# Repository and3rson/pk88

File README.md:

# PK88

Single-board computer based on KM1810VM88 CPU (Ukrainian clone of Intel 8088) that can run ELKS!

PK stands for Персональний Комп'ютер ("Personalnii Kompyuter", i.e. "Personal Computer") in Ukrainian.

This board runs @ 8 MHz (24 MHz oscillator) in minimum mode.

- [KiCad schematics](./kicad)
- [GAL sources](./gal) - Address & I/O port decoders using 2x ATF16V8
- [Various circuit simulations](./circuits) - made with [Digital](https://github.com/hneemann/Digital)
- [MetalBIOS](./metalbios) - IBM PC XT compatible-ish BIOS that I made specifically for PK-88

## Resources

- 8088/x86 instruction set: <https://zsmith.co/intel.php>
- Zen of Assembly language (including 8088 instruction set): <http://www.jagregory.com/abrash-zen-of-asm/>
- Soviet IC series differences: <http://vozom.ho.ua/R4/page21.html>
- IBM PC technical reference: <http://bitsavers.informatik.uni-stuttgart.de/pdf/ibm/pc/at/6183355_PC_AT_Technical_Reference_Mar86.pdf>

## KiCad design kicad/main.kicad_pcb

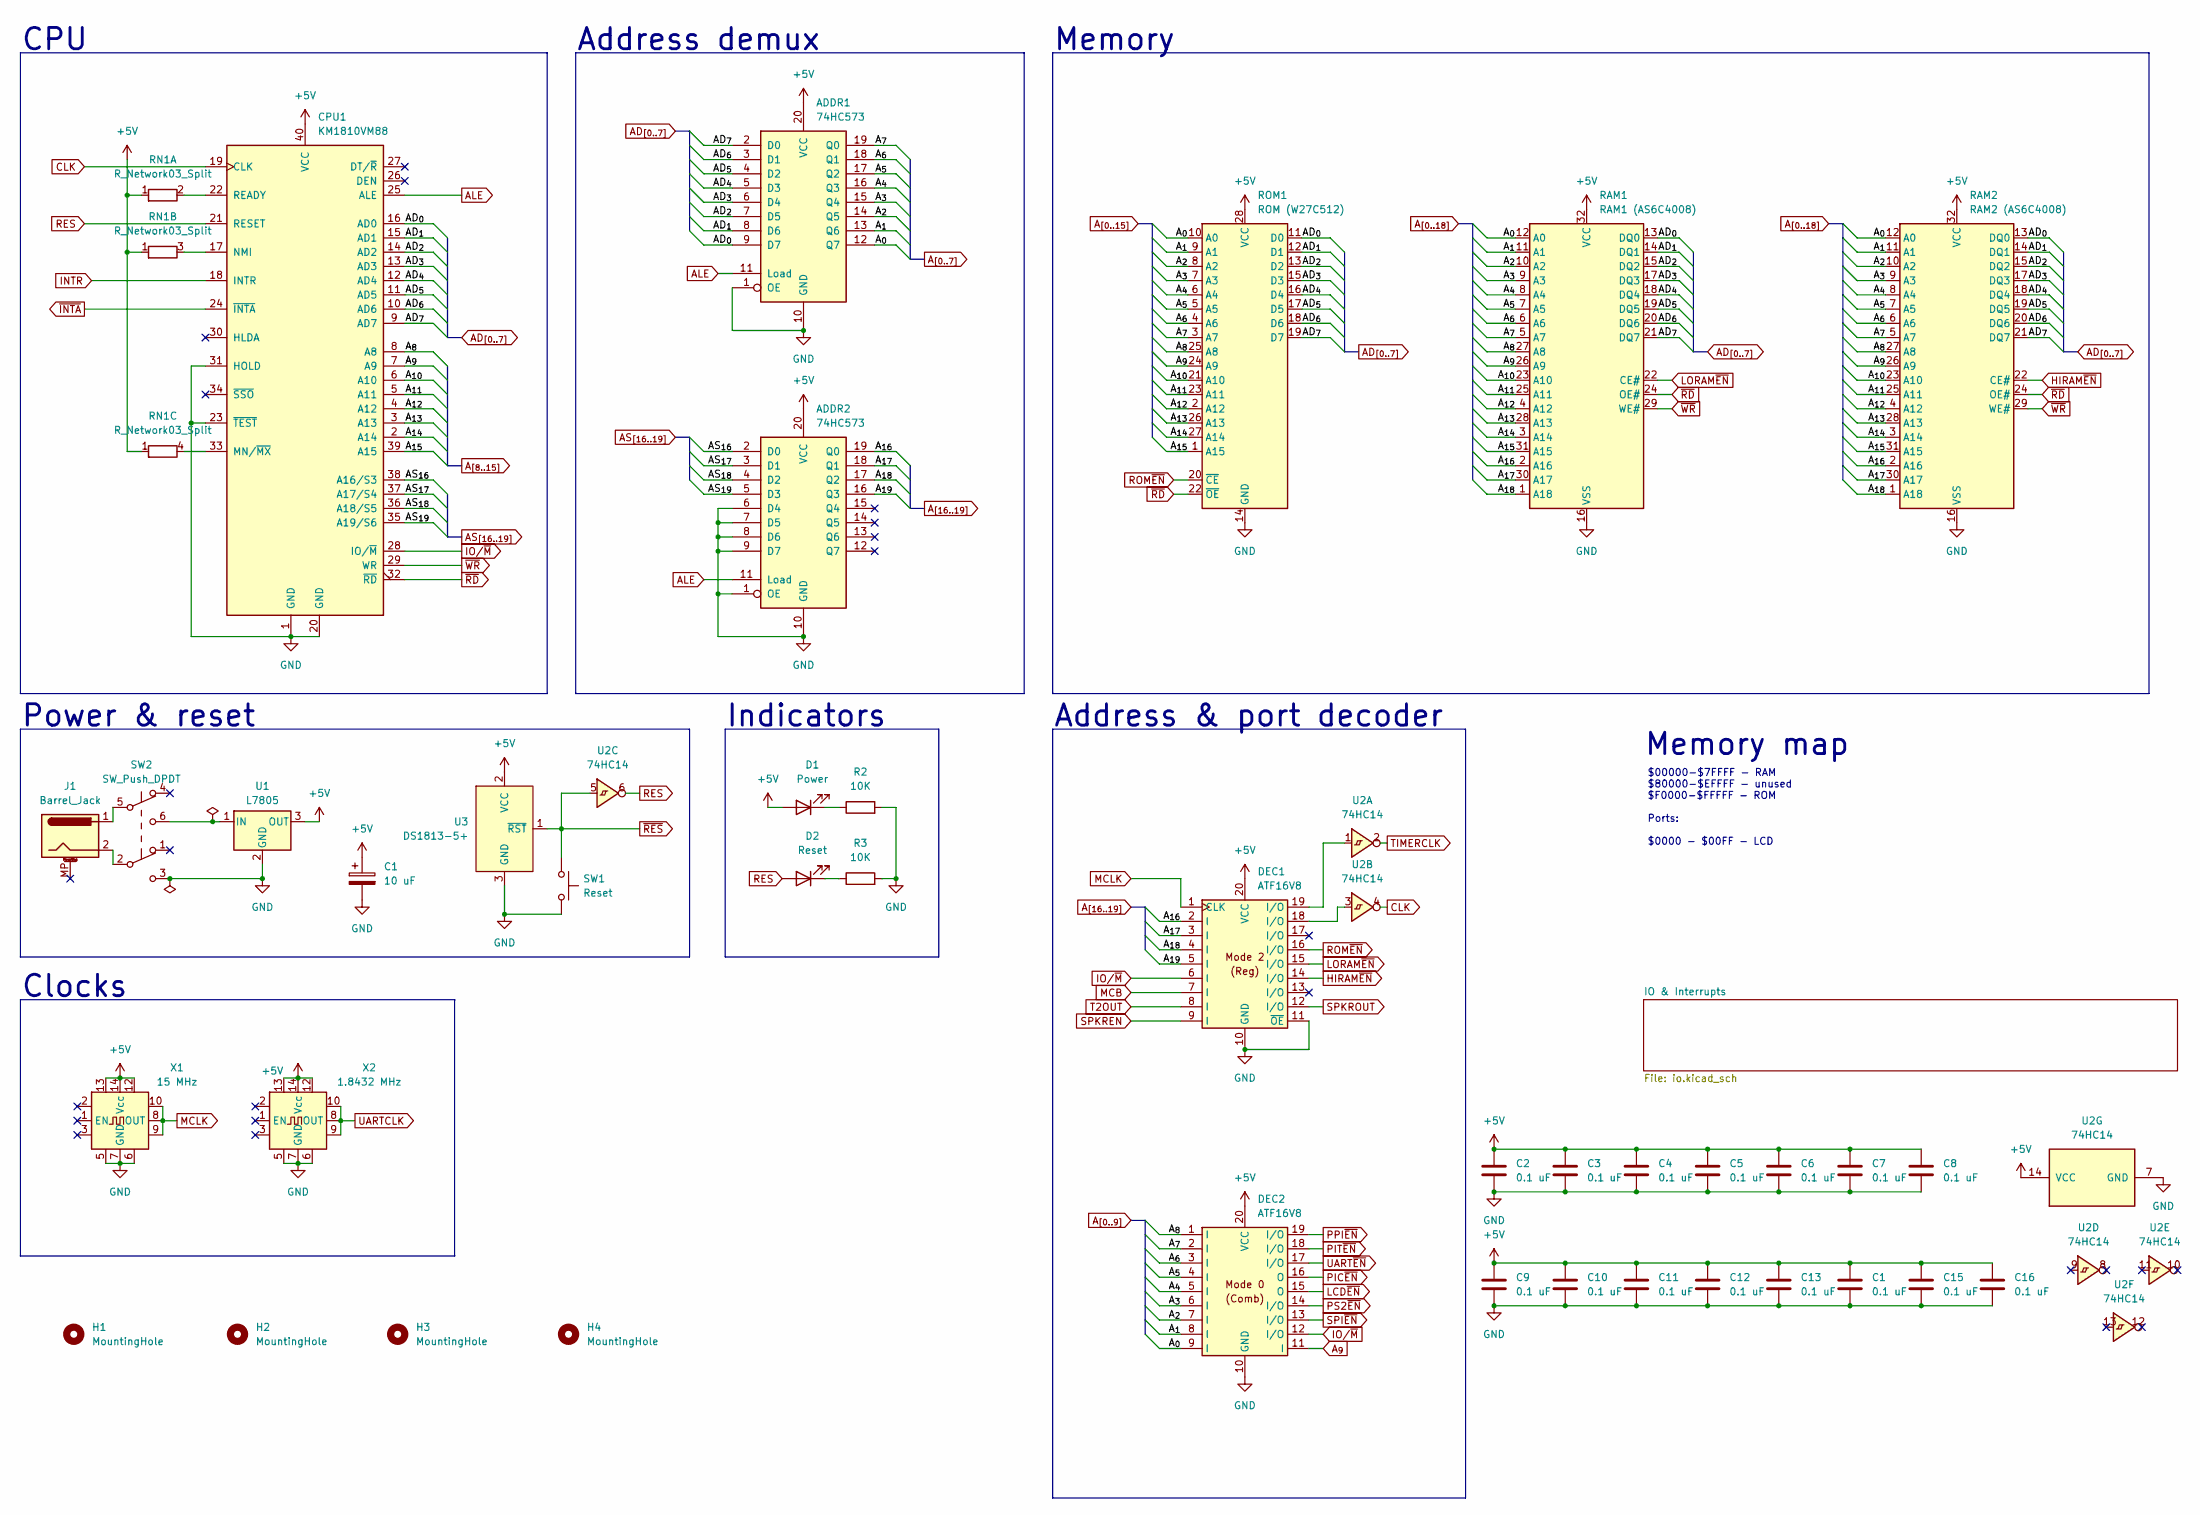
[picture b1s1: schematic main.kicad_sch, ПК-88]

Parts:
ADDR1, ADDR2: 74HC573; DIP-20_W7.62mm_Socket
C1: 10 uF; CP_Radial_D8.0mm_P3.50mm
C2, C4, C5, C7, C8, C10, C15, C16: 0.1 uF; C_Disc_Long
C3, C11: 0.1 uF; C_Disc_D3.0mm_W1.6mm_P2.50mm
C6, C9, C12, C13: 0.1 uF; C_Disc_VeryLong
CPU1: KM1810VM88; DIP-40_W15.24mm
D1: Power; LED_D3.0mm
D2: Reset; LED_D3.0mm
DEC1, DEC2: ATF16V8; DIP-20_W7.62mm_Socket
H1, H2, H3, H4: MountingHole; Hole_3.5x5
J1: Barrel_Jack; BarrelJack_Wuerth_6941xx301002
R2, R3: 10K; R_Axial_DIN0204_L3.6mm_D1.6mm_P7.62mm_Horizontal
RAM1: RAM1 (AS6C4008); DIP-32_W15.24mm
RAM2: RAM2 (AS6C4008); DIP-32_W15.24mm
RN1: R_Network03_Split; R_Array_SIP4
ROM1: ROM (W27C512); ZIF28
SW1: Reset; SW_PUSH_6mm_H5mm
SW2: SW_Push_DPDT; PB22E06
U1: L7805; TO-220-3_Vertical
U2: 74HC14; DIP-14_W7.62mm_Socket
U3: DS1813-5+; TO-92L_Inline_Wide
X1: 15 MHz; Oscillator_DIP-8-14
X2: 1.8432 MHz; Oscillator_DIP-8-14

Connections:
+5V: ADDR1.20 (VCC), ADDR2.20 (VCC), C1.1, C2.1, C3.1, C4.1, C5.1, C6.1, C7.1, C8.1, C9.1, C10.1, C11.1, C12.1, C13.1, C15.1, C16.1, CPU1.40 (VCC), D1.2 (A), DEC1.20 (VCC), DEC2.20 (VCC), RAM1.32 (VCC), RAM2.32 (VCC), RN1.1 (R1), ROM1.28 (VCC), U1.3 (OUT), U2.14 (VCC), U3.2 (VCC), X1.12, X1.13, X1.14 (Vcc), X2.12, X2.13, X2.14 (Vcc); also elsewhere on the board
AD_{0}: ADDR1.9 (D7), CPU1.16 (AD0), RAM1.13 (DQ0), RAM2.13 (DQ0), ROM1.11 (D0); also elsewhere on the board
AD_{1}: ADDR1.8 (D6), CPU1.15 (AD1), RAM1.14 (DQ1), RAM2.14 (DQ1), ROM1.12 (D1); also elsewhere on the board
AD_{2}: ADDR1.7 (D5), CPU1.14 (AD2), RAM1.15 (DQ2), RAM2.15 (DQ2), ROM1.13 (D2); also elsewhere on the board
AD_{3}: ADDR1.6 (D4), CPU1.13 (AD3), RAM1.17 (DQ3), RAM2.17 (DQ3), ROM1.15 (D3); also elsewhere on the board
AD_{4}: ADDR1.5 (D3), CPU1.12 (AD4), RAM1.18 (DQ4), RAM2.18 (DQ4), ROM1.16 (D4); also elsewhere on the board
AD_{5}: ADDR1.4 (D2), CPU1.11 (AD5), RAM1.19 (DQ5), RAM2.19 (DQ5), ROM1.17 (D5); also elsewhere on the board
AD_{6}: ADDR1.3 (D1), CPU1.10 (AD6), RAM1.20 (DQ6), RAM2.20 (DQ6), ROM1.18 (D6); also elsewhere on the board
AD_{7}: ADDR1.2 (D0), CPU1.9 (AD7), RAM1.21 (DQ7), RAM2.21 (DQ7), ROM1.19 (D7); also elsewhere on the board
ALE: ADDR1.11 (Load), ADDR2.11 (Load), CPU1.25 (ALE)
AS_{16}: ADDR2.2 (D0), CPU1.38 (A16/S3)
AS_{17}: ADDR2.3 (D1), CPU1.37 (A17/S4)
AS_{18}: ADDR2.4 (D2), CPU1.36 (A18/S5)
AS_{19}: ADDR2.5 (D3), CPU1.35 (A19/S6)
A_{0}: ADDR1.12 (Q7), DEC2.9 (I), RAM1.12 (A0), RAM2.12 (A0), ROM1.10 (A0); also elsewhere on the board
A_{1}: ADDR1.13 (Q6), DEC2.8 (I), RAM1.11 (A1), RAM2.11 (A1), ROM1.9 (A1); also elsewhere on the board
A_{2}: ADDR1.14 (Q5), DEC2.7 (I), RAM1.10 (A2), RAM2.10 (A2), ROM1.8 (A2); also elsewhere on the board
A_{3}: ADDR1.15 (Q4), DEC2.6 (I), RAM1.9 (A3), RAM2.9 (A3), ROM1.7 (A3)
A_{4}: ADDR1.16 (Q3), DEC2.5 (I), RAM1.8 (A4), RAM2.8 (A4), ROM1.6 (A4)
A_{5}: ADDR1.17 (Q2), DEC2.4 (I), RAM1.7 (A5), RAM2.7 (A5), ROM1.5 (A5)
A_{6}: ADDR1.18 (Q1), DEC2.3 (I), RAM1.6 (A6), RAM2.6 (A6), ROM1.4 (A6)
A_{7}: ADDR1.19 (Q0), DEC2.2 (I), RAM1.5 (A7), RAM2.5 (A7), ROM1.3 (A7)
A_{8}: CPU1.8 (A8), DEC2.1 (I), RAM1.27 (A8), RAM2.27 (A8), ROM1.25 (A8)
A_{9}: CPU1.7 (A9), DEC2.11 (I), RAM1.26 (A9), RAM2.26 (A9), ROM1.24 (A9)
A_{10}: CPU1.6 (A10), RAM1.23 (A10), RAM2.23 (A10), ROM1.21 (A10)
A_{11}: CPU1.5 (A11), RAM1.25 (A11), RAM2.25 (A11), ROM1.23 (A11)
A_{12}: CPU1.4 (A12), RAM1.4 (A12), RAM2.4 (A12), ROM1.2 (A12)
A_{13}: CPU1.3 (A13), RAM1.28 (A13), RAM2.28 (A13), ROM1.26 (A13)
A_{14}: CPU1.2 (A14), RAM1.3 (A14), RAM2.3 (A14), ROM1.27 (A14)
A_{15}: CPU1.39 (A15), RAM1.31 (A15), RAM2.31 (A15), ROM1.1 (A15)
A_{16}: ADDR2.19 (Q0), DEC1.2 (I), RAM1.2 (A16), RAM2.2 (A16)
A_{17}: ADDR2.18 (Q1), DEC1.3 (I), RAM1.30 (A17), RAM2.30 (A17)
A_{18}: ADDR2.17 (Q2), DEC1.4 (I), RAM1.1 (A18), RAM2.1 (A18)
A_{19}: ADDR2.16 (Q3), DEC1.5 (I)
CLK: CPU1.19 (CLK), U2.4; also elsewhere on the board
HIRAM~EN: DEC1.14 (I/O), RAM2.22 (CE#)
INTR: CPU1.18 (INTR); also elsewhere on the board
IO/~M: CPU1.28 (IO/~M), DEC1.6 (I), DEC2.12 (I/O)
LCD~EN: DEC2.15 (O); also elsewhere on the board
LORAM~EN: DEC1.15 (I/O), RAM1.22 (CE#)
MCLK: DEC1.1 (CLK), X1.8 (OUT), X1.9, X1.10
unnamed: CPU1.33 (MN/~MX), RN1.4 (R3.2)
unnamed: CPU1.17 (NMI), RN1.3 (R2.2)
unnamed: CPU1.22 (READY), RN1.2 (R1.2)
unnamed: D2.1 (K), R3.1
unnamed: DEC1.18 (I/O), U2.3
unnamed: DEC1.19 (I/O), U2.1
unnamed: J1.1, SW2.5 (B)
unnamed: J1.2, SW2.2 (B)
unnamed: SW2.6 (C), U1.1 (IN)
PIC~EN: DEC2.16 (O); also elsewhere on the board
PIT~EN: DEC2.18 (I/O); also elsewhere on the board
PPI~EN: DEC2.19 (I/O); also elsewhere on the board
PS2~EN: DEC2.14 (I/O); also elsewhere on the board
RES: CPU1.21 (RESET), D2.2 (A), U2.6; also elsewhere on the board
ROM~EN: DEC1.16 (I/O), ROM1.20 (~CE)
SPI~EN: DEC2.13 (I/O); also elsewhere on the board
SPKREN: DEC1.9 (I); also elsewhere on the board
SPKROUT: DEC1.12 (I/O); also elsewhere on the board
T2OUT: DEC1.8 (I); also elsewhere on the board
TIMERCLK: U2.2; also elsewhere on the board
UARTCLK: X2.8 (OUT), X2.9, X2.10; also elsewhere on the board
UART~EN: DEC2.17 (I/O); also elsewhere on the board
~INTA: CPU1.24 (~INTA); also elsewhere on the board
~RD: CPU1.32 (~RD), RAM1.24 (OE#), RAM2.24 (OE#), ROM1.22 (~OE); also elsewhere on the board
~RES: SW1.1, U2.5, U3.1 (~RST); also elsewhere on the board
~WR: CPU1.29 (WR), RAM1.29 (WE#), RAM2.29 (WE#); also elsewhere on the board

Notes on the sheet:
Address & port decoder
Clocks
Power & reset
Address demux
Indicators
Memory
$00000-$7FFFF - RAM $80000-$EFFFF - unused $F0000-$FFFFF - ROM Ports: $0000 - $00FF - LCD
Memory map
CPU

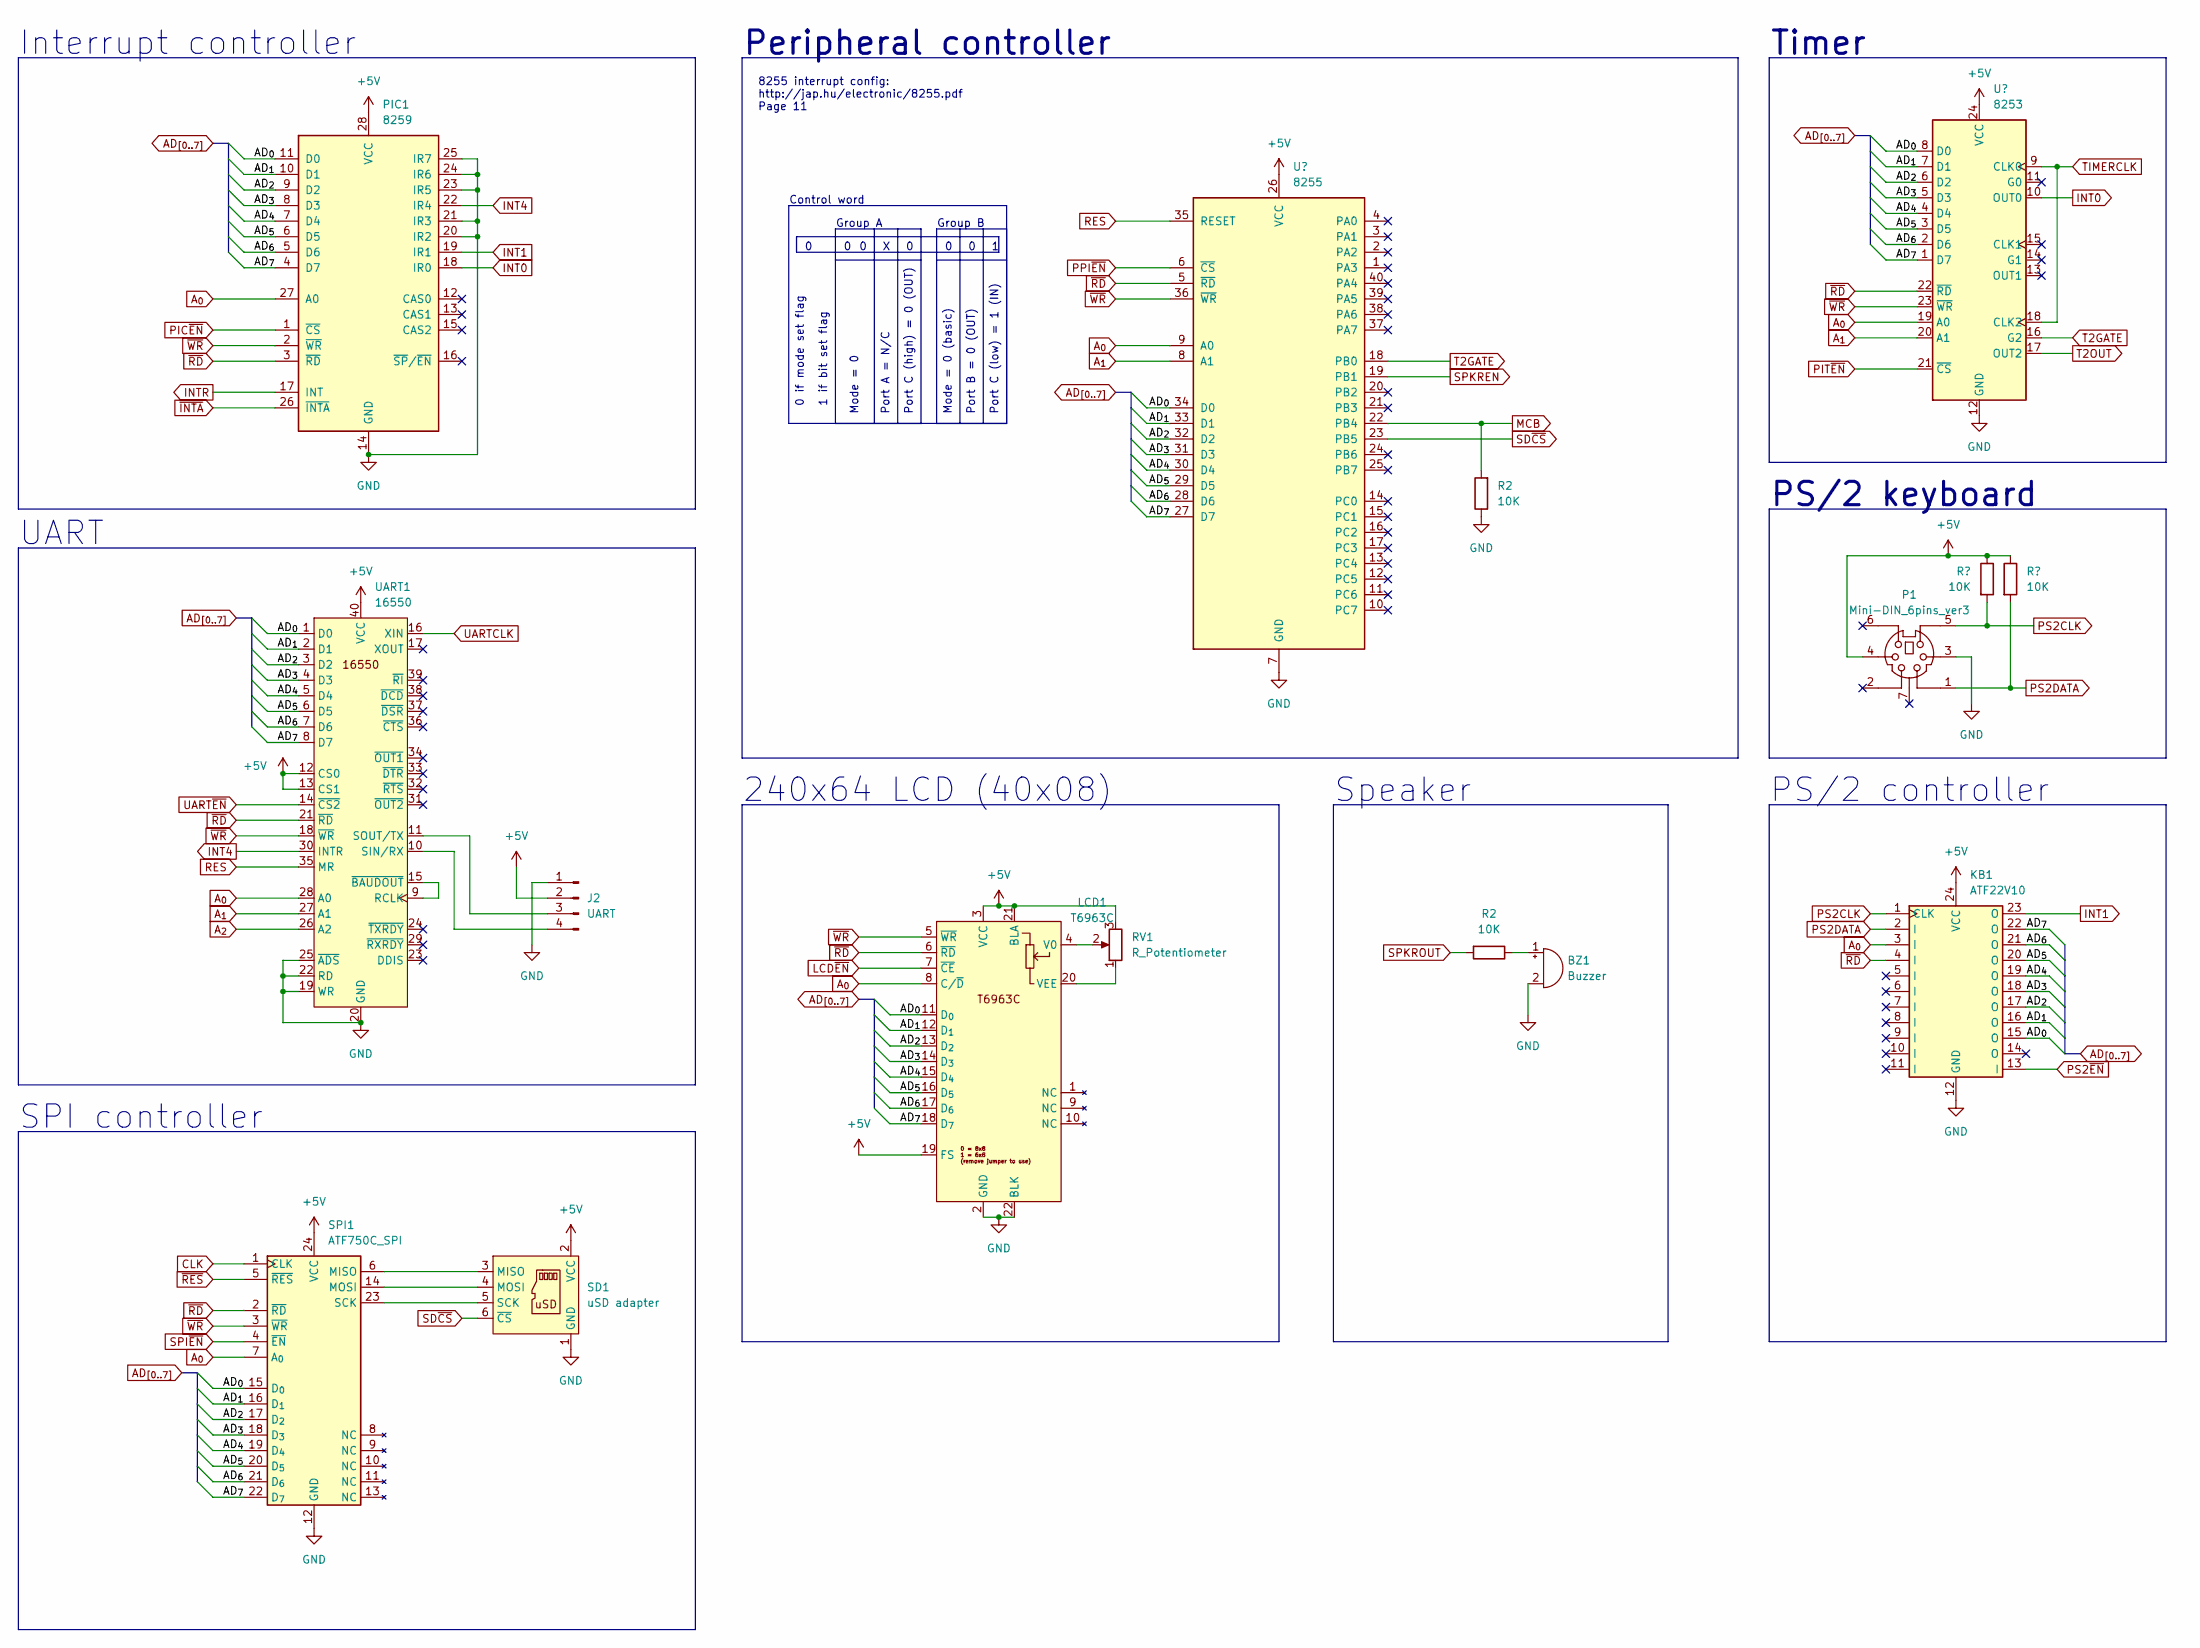
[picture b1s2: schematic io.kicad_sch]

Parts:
BZ1: Buzzer; Buzzer_TDK_PS1240P02BT_D12.2mm_H6.5mm
J2: UART; PinHeader_1x04_P2.54mm_Vertical
KB1: ATF22V10; DIP-24_W7.62mm_Socket
LCD1: T6963C; LCD240128_TFT_var2
P1: Mini-DIN_6pins_ver3; Connector_Mini-DIN_Female_6Pin_2rows
PIC1: 8259; DIP-28_W15.24mm_Socket
PIT1: 8253; DIP-24_W15.24mm
PPI1: 8255; DIP-40_W15.24mm
R2, R4, R5: 10K; R_Axial_DIN0204_L3.6mm_D1.6mm_P7.62mm_Horizontal
RV1: R_Potentiometer; Potentiometer_Bourns_3296Y_Vertical
SD1: uSD adapter; MicroSD-Adapter
SPI1: ATF750C_SPI; DIP-24_W7.62mm_Socket
UART1: 16550; DIP-40_W15.24mm_Socket

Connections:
+5V: J2.2, KB1.24 (VCC), LCD1.3 (VCC), LCD1.19 (FS), LCD1.21 (BLA), P1.4, PIC1.28 (VCC), PIT1.24 (VCC), PPI1.26 (VCC), R4.1, R5.1, RV1.3, SD1.2 (VCC), SPI1.24 (VCC), UART1.12 (CS0), UART1.13 (CS1), UART1.40 (VCC); also elsewhere on the board
AD_{0}: KB1.15 (O), LCD1.11 (D_{0}), PIC1.11 (D0), PIT1.8 (D0), PPI1.34 (D0), SPI1.15 (D_{0}), UART1.1 (D0); also elsewhere on the board
AD_{1}: KB1.16 (O), LCD1.12 (D_{1}), PIC1.10 (D1), PIT1.7 (D1), PPI1.33 (D1), SPI1.16 (D_{1}), UART1.2 (D1); also elsewhere on the board
AD_{2}: KB1.17 (O), LCD1.13 (D_{2}), PIC1.9 (D2), PIT1.6 (D2), PPI1.32 (D2), SPI1.17 (D_{2}), UART1.3 (D2); also elsewhere on the board
AD_{3}: KB1.18 (O), LCD1.14 (D_{3}), PIC1.8 (D3), PIT1.5 (D3), PPI1.31 (D3), SPI1.18 (D_{3}), UART1.4 (D3); also elsewhere on the board
AD_{4}: KB1.19 (O), LCD1.15 (D_{4}), PIC1.7 (D4), PIT1.4 (D4), PPI1.30 (D4), SPI1.19 (D_{4}), UART1.5 (D4); also elsewhere on the board
AD_{5}: KB1.20 (O), LCD1.16 (D_{5}), PIC1.6 (D5), PIT1.3 (D5), PPI1.29 (D5), SPI1.20 (D_{5}), UART1.6 (D5); also elsewhere on the board
AD_{6}: KB1.21 (O), LCD1.17 (D_{6}), PIC1.5 (D6), PIT1.2 (D6), PPI1.28 (D6), SPI1.21 (D_{6}), UART1.7 (D6); also elsewhere on the board
AD_{7}: KB1.22 (O), LCD1.18 (D_{7}), PIC1.4 (D7), PIT1.1 (D7), PPI1.27 (D7), SPI1.22 (D_{7}), UART1.8 (D7); also elsewhere on the board
A_{0}: KB1.3 (I), LCD1.8 (C/~D), PIC1.27 (A0), PIT1.19 (A0), PPI1.9 (A0), SPI1.7 (A_{0}), UART1.28 (A0); also elsewhere on the board
A_{1}: PIT1.20 (A1), PPI1.8 (A1), UART1.27 (A1); also elsewhere on the board
A_{2}: UART1.26 (A2); also elsewhere on the board
CLK: SPI1.1 (CLK); also elsewhere on the board
INT0: PIC1.18 (IR0), PIT1.10 (OUT0)
INT1: KB1.23 (O), PIC1.19 (IR1)
INT4: PIC1.22 (IR4), UART1.30 (INTR)
INTR: PIC1.17 (INT); also elsewhere on the board
LCD~EN: LCD1.7 (~CE); also elsewhere on the board
unnamed: J2.3, UART1.11 (SOUT/TX)
unnamed: J2.4, UART1.10 (SIN/RX)
unnamed: LCD1.4 (V0), RV1.2
unnamed: LCD1.20 (VEE), RV1.1
unnamed: SD1.3 (MISO), SPI1.6 (MISO)
unnamed: SD1.4 (MOSI), SPI1.14 (MOSI)
unnamed: SD1.5 (SCK), SPI1.23 (SCK)
unnamed: UART1.9 (RCLK), UART1.15 (~BAUDOUT)
PIC~EN: PIC1.1 (~CS); also elsewhere on the board
PIT~EN: PIT1.21 (~CS); also elsewhere on the board
PPI~EN: PPI1.6 (~CS); also elsewhere on the board
PS2CLK: KB1.1 (CLK), P1.5, R4.2
PS2DATA: KB1.2 (I), P1.1, R5.2
PS2~EN: KB1.13 (I); also elsewhere on the board
RES: PPI1.35 (RESET), UART1.35 (MR); also elsewhere on the board
SD~CS: PPI1.23 (PB5), SD1.6 (~CS)
SPI~EN: SPI1.4 (~EN); also elsewhere on the board
SPKREN: PPI1.19 (PB1); also elsewhere on the board
T2GATE: PIT1.16 (G2), PPI1.18 (PB0)
T2OUT: PIT1.17 (OUT2); also elsewhere on the board
TIMERCLK: PIT1.9 (CLK0), PIT1.18 (CLK2); also elsewhere on the board
UARTCLK: UART1.16 (XIN); also elsewhere on the board
UART~EN: UART1.14 (~CS2); also elsewhere on the board
~INTA: PIC1.26 (~INTA); also elsewhere on the board
~RD: KB1.4 (I), LCD1.6 (~RD), PIC1.3 (~RD), PIT1.22 (~RD), PPI1.5 (~RD), SPI1.2 (~RD), UART1.21 (~RD); also elsewhere on the board
~RES: SPI1.5 (~RES); also elsewhere on the board
~WR: LCD1.5 (~WR), PIC1.2 (~WR), PIT1.23 (~WR), PPI1.36 (~WR), SPI1.3 (~WR), UART1.18 (~WR); also elsewhere on the board

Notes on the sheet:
0 if mode set flag
Speaker
SPI controller
Timer
Mode = 0
PS/2 controller
240x64 LCD (40x08)
Mode = 0 (basic)
Interrupt controller
Peripheral controller
Group A
Control word
Group B
1 if bit set flag
Port B = 0 (OUT)
Port C (high) = 0 (OUT)
Port A = N/C
UART
8255 interrupt config: http://jap.hu/electronic/8255.pdf Page 11
PS/2 keyboard
Port C (low) = 1 (IN)

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
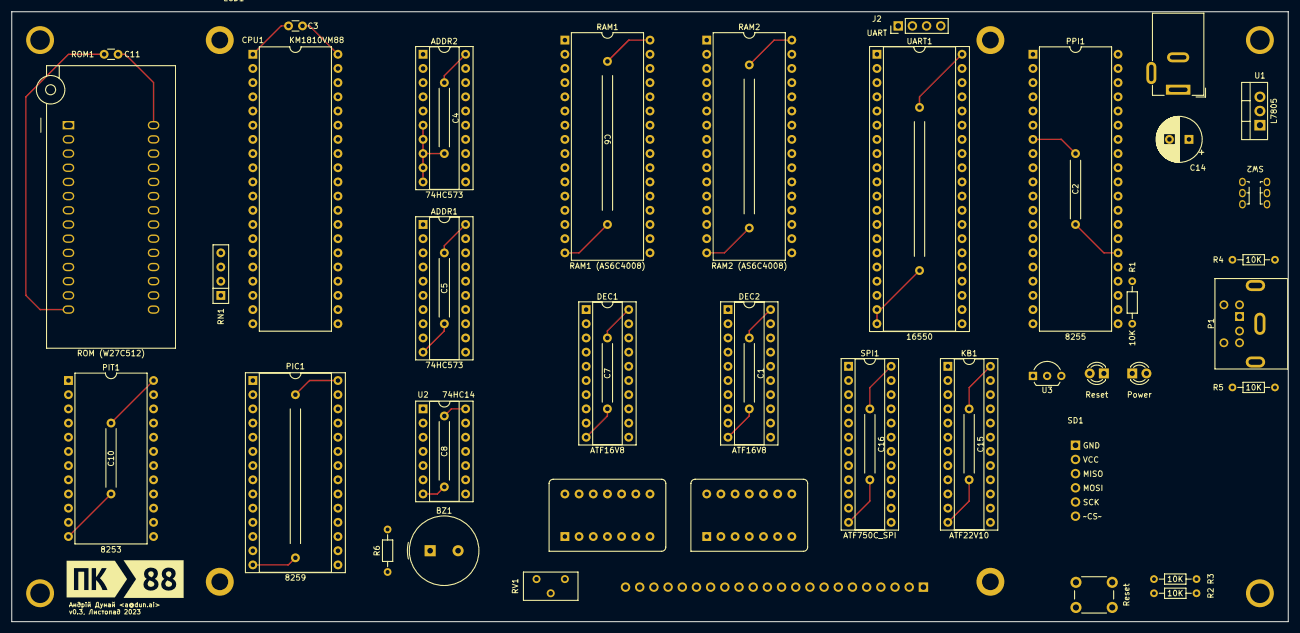
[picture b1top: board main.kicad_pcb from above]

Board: 2 copper layers, 228.6 x 109.2 mm, 59 parts (0 on the bottom side), 86 nets.

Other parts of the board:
C14: 10 uF; CP_Radial_D8.0mm_P3.50mm
R1, R6: 10K; R_Axial_DIN0204_L3.6mm_D1.6mm_P7.62mm_Horizontal
kibuzzard-65254FD7: G***; kibuzzard-65254FD7
kibuzzard-65254FDB: G***; kibuzzard-65254FDB

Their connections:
+5V: C14.1; also elsewhere on the board
SPKROUT: R6.2; also elsewhere on the board

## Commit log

2023-09-23 Initial schematic
2023-09-25 First prototype without I/O
2023-09-25 Add interrupt controller & display
2023-09-25 Initial ROM assembly
2023-09-26 Add parallel port
2023-09-26 ROM code updates
2023-09-27 Add Freerouting PCB
2023-09-27 Corrected version of v1 PCB
2023-09-28 Mark as v02
2023-09-28 Add image & PDF
2023-09-28 Update images
2023-09-28 Update PDF
2023-09-28 Update PCB image
2023-09-28 Update PCB
2023-09-28 Add 3D render
2023-09-29 Add I/O sheet
2023-09-29 Fix HOLD, INT & address decoder equations
2023-09-29 Tie HOLD low, add GAL simulation for clock, add 8253 clock
2023-09-30 Add links to README
2023-09-30 Add LCD driver
2023-10-01 Add 8251 USART
2023-10-01 Add UART
2023-10-01 Fix LCD code
2023-10-01 Cleanup asm code
2023-10-01 Cleanup ASM dir structure
2023-10-02 Cleanup comments
2023-10-02 Update ROM code
2023-10-02 Init DS segment
2023-10-02 Add UART & uSD card
2023-10-03 Update symbols
2023-10-03 Move chips to center/bottom
2023-10-04 Implement 0x50 syscall
2023-10-04 Update PCB label
2023-10-04 Realign assembly code
2023-10-05 Add skeleton for MetalBIOS
2023-10-05 WIP - int13h
2023-10-05 Use GNU LD as linker
2023-10-06 Cleanup Makefile & includes
2023-10-06 WIP: int 13h implementation for uSD card with virtual CHS geometry
2023-10-06 Move disk code into separate module, add int 16h
2023-10-06 Add 8259 interrupt controller, update PCB
2023-10-08 135x160 board
2023-10-09 Add second GAL
2023-10-09 Fix equations
2023-10-09 PCB 2.0 RC
2023-10-10 Cleaner PCB
2023-10-10 Even better PCB
2023-10-10 Update logo
2023-10-10 Final PCB
2023-10-10 Add RTC interrupt stub
2023-10-11 New PCB (add MCB line)
2023-10-13 Add T6963 deiver, fix PPI address in I/O decoder, fix T6963C symbol
2023-10-13 Cleanup docstrings
2023-10-13 Basic UART support
2023-10-14 Add BIOS int 14h (serial port)
2023-10-14 Fix disasm rule
2023-10-14 Implement UART receive
2023-10-14 Add basic BDA addresses (equipment list, video mode, com port address)
2023-10-15 Rename ROM to MetalBIOS
2023-10-15 READMEs are hard
2023-11-09 Add comments to UART init code
2023-11-10 Add SD card support, fix LCD init sequence
2023-11-11 Implement sector reading from SD card, add CR/LF handling to LCD
2023-11-11 Add custom fonts
2023-11-11 WIP: cp1251
2023-11-11 Add init code for 8253 PIT, reduce PIT speed to 1/4 of CPU speed
2023-11-13 Add memtest & hex printing functions
2023-11-16 Implement SD card writing
2023-11-18 Add unimplemented interrupt notifications, add Ukrainian font
2023-11-18 Improve SPI read function
2023-11-18 Cleanup startup screen
2023-11-18 Remove unnecessary comment
2023-11-18 Improve SPI performance
2023-11-19 Init registers before executing bootloader
2023-11-19 Set/clear carry flags in BIOS calls
2023-11-19 Add macro to set carry flag in interrupts
2023-11-20 Implement disk geometry function, update SD card geometry
2023-11-20 Fix interrupts clobbering bx register, first ELKS test
2023-11-21 Add LCD scrolling
2023-11-21 Improve SPI read speed
2023-11-21 ELKS works!
2023-11-25 PS/2 with GAL - finally
2023-11-26 V0.3 WIP
2023-11-26 WIP: PCB v3.0
2023-11-29 Add cupl & jed2eqn
2023-11-29 Cleanup
2023-11-29 Fix make rules for cupl
2023-11-29 Proper PS/2 keyboard support through ATF22V10 (no ring buffer yet)
2023-11-29 WIP: SPI
2023-11-30 Final SPI equations
2023-11-30 Add SPI controller to PCB v0.3
2023-12-01 Fix nasty bug with gotoxy not setting ES properly
2023-12-01 Fix symbol descriptions
2023-12-01 Fix int 10h function 0ah
2023-12-01 Shifted keys for PS/2 keyboard
2023-12-01 Implement proper screen scrolling (int 10h, functions 06h & 07h)
2023-12-02 Fix BIOS screen scrolling (int 10h, function 06h)
2023-12-02 Add arrow key codes (extended PS/2 codes)
2023-12-02 Add ctrl keymap
2023-12-02 WIP - PCB v0.4
2023-12-04 Add INT 0x88 homebrew API
2023-12-04 Add CTRL-Break handler
2023-12-04 Boot system by using INT 0x19
2023-12-04 Refactor keyboard code
2023-12-04 Switch to yasm
2023-12-04 Switch back to nasm since yasm does not generate proper dep files
2023-12-05 Fixed dependency generation with yasm
2023-12-05 Fix typo
2023-12-07 Add -Werror
2023-12-11 Cleanup linker script
